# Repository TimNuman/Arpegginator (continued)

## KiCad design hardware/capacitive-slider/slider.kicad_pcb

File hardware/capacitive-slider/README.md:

# Capacitive Touch Slider — AT42QT2120

Hardware design for a no-moving-parts capacitive touch slider PCB that replaces
the on-screen TouchStrip in the Arpegginator. Connects to Teensy 4.1 over I2C.

## Overview

- **IC**: Microchip AT42QT2120 (12-channel capacitive touch controller)
- **Interface**: I2C (addr 0x1C), up to 400 kHz
- **Supply**: 1.8–5.5 V (run at 3.3 V from Teensy)
- **Output**: Per-key touch status + interpolated slider position
- **Slider channels**: 8 keys configured as a slider (keys 0–7)
- **Extra keys**: Keys 8–11 available for discrete buttons (play, stop, shift, etc.)

## Slider Pad Patterns

Three pattern options are provided below. All assume a **100 mm active length**
and **10 mm PCB width**, single-layer copper on the top side with ground fill on
the bottom.

---

### Pattern A: Interleaved Diamonds (Recommended)

The standard pattern from Microchip's application notes. Best balance of
linearity and noise immunity.

```
  Key0  Key1  Key2  Key3  Key4  Key5  Key6  Key7
  ┌─────────────────────────────────────────────────┐
  │  ◇   ◇   ◇   ◇   ◇   ◇   ◇   ◇   ◇   ◇   ◇  │
  │ ◇ ◇ ◇ ◇ ◇ ◇ ◇ ◇ ◇ ◇ ◇ ◇ ◇ ◇ ◇ ◇ ◇ ◇ ◇ ◇ ◇  │
  │  ◇   ◇   ◇   ◇   ◇   ◇   ◇   ◇   ◇   ◇   ◇  │
  └─────────────────────────────────────────────────┘

  Cross-section (one repeat unit):

      ┌───┐       ┌───┐
     /  A  \     /  B  \        A and B are adjacent channels
    /       \   /       \       Diamond tips interleave
   /    ◆    \ /    ◆    \     so A's falling edge overlaps B's
  /           X           \    rising edge — enables interpolation
  \          / \          /
   \        /   \        /
    \      /     \      /
     \    /       \    /
      \  /         \  /
       \/           \/
```

**Dimensions per diamond:**
- Diamond width: 10 mm (along slider axis)
- Diamond height: 8 mm (across slider width)
- Overlap between adjacent keys: 2.5 mm
- Pitch (center-to-center): 12.5 mm
- Gap between copper edges: 0.3 mm
- 8 keys x 12.5 mm = 100 mm active length

**Trace routing:** Each diamond connects via a thin trace (0.2 mm) routed on the
same layer to the AT42QT2120 pin. Keep traces short and add a ground guard ring
around each trace.

---

### Pattern B: Chevron / Zigzag

Higher edge density gives better sensitivity for lighter touches. Slightly more
complex to route.

```
  Key0  Key1  Key2  Key3  Key4  Key5  Key6  Key7
  ┌─────────────────────────────────────────────────┐
  │ /\/\/\/\/\/\/\/\/\/\/\/\/\/\/\/\/\/\/\/\/\/\/\  │
  │ \/\/\/\/\/\/\/\/\/\/\/\/\/\/\/\/\/\/\/\/\/\/\/  │
  │ /\/\/\/\/\/\/\/\/\/\/\/\/\/\/\/\/\/\/\/\/\/\/\  │
  │ \/\/\/\/\/\/\/\/\/\/\/\/\/\/\/\/\/\/\/\/\/\/\/  │
  └─────────────────────────────────────────────────┘

  Cross-section:

  Channel A    Channel B
    /\    /\    /\    /\
   /  \  /  \  /  \  /  \
  /  A \/  B \/  A \/  B \    Interlocking zigzag teeth
  \    /\    /\    /\    /    3-4 teeth per channel
   \  /  \  /  \  /  \  /
    \/    \/    \/    \/
```

**Dimensions:**
- Tooth height: 4 mm
- Tooth pitch: 2.5 mm
- 3 teeth per key, keys spaced at 12.5 mm
- Gap: 0.3 mm

---

### Pattern C: Simple Rectangular Bars

Easiest to lay out. Lower interpolation quality but perfectly adequate for
scrolling. Good starting point if this is your first capacitive PCB.

```
  Key0  Key1  Key2  Key3  Key4  Key5  Key6  Key7
  ┌─────────────────────────────────────────────────┐
  │ ████  ████  ████  ████  ████  ████  ████  ████ │
  │ ████  ████  ████  ████  ████  ████  ████  ████ │
  │ ████  ████  ████  ████  ████  ████  ████  ████ │
  └─────────────────────────────────────────────────┘

  Cross-section:

  ┌──────┐ ┌──────┐ ┌──────┐
  │      │ │      │ │      │   Simple rectangular pads
  │  A   │ │  B   │ │  C   │   with gaps between them.
  │      │ │      │ │      │   Interpolation uses signal
  └──────┘ └──────┘ └──────┘   strength ratio of neighbors.
     gap      gap      gap
```

**Dimensions:**
- Pad width: 11 mm (along slider axis)
- Pad height: 8 mm
- Gap: 1.5 mm
- Pitch: 12.5 mm

---

## Schematic

```
                          AT42QT2120
                     ┌──────────────────┐
  Teensy SDA ───────┤ SDA          KEY0 ├─── Slider pad 0
  Teensy SCL ───────┤ SCL          KEY1 ├─── Slider pad 1
                    │              KEY2 ├─── Slider pad 2
  3.3V ──┬─────────┤ VDD          KEY3 ├─── Slider pad 3
         │  100nF  │              KEY4 ├─── Slider pad 4
         ├──||─────┤ VSS (GND)    KEY5 ├─── Slider pad 5
         │         │              KEY6 ├─── Slider pad 6
  GND ───┴─────────┤ VSS          KEY7 ├─── Slider pad 7
                    │                   │
                    │ CHANGE# ──────────┼─── Teensy GPIO (interrupt)
                    │                   │
                    │ KEY8  ─────────── ┼─── (optional: Play btn)
                    │ KEY9  ─────────── ┼─── (optional: Stop btn)
                    │ KEY10 ─────────── ┼─── (optional: Shift btn)
                    │ KEY11 ─────────── ┼─── (optional: Mode btn)
                    │                   │
                    │ MODE  ─────────── ┼─── GND (I2C mode)
                    └──────────────────┘

  Pull-ups: 4.7 kOhm on SDA and SCL to 3.3V
  Decoupling: 100 nF + 10 uF on VDD/VSS
```

## Bill of Materials

| Ref  | Part              | Package    | Qty | Notes                         |
|------|-------------------|------------|-----|-------------------------------|
| U1   | AT42QT2120-MMH    | QFN-24     | 1   | Capacitive touch controller   |
| C1   | 100 nF ceramic    | 0402/0603  | 1   | VDD decoupling                |
| C2   | 10 uF ceramic     | 0805       | 1   | VDD bulk decoupling           |
| R1   | 4.7 kOhm         | 0402/0603  | 1   | I2C SDA pull-up               |
| R2   | 4.7 kOhm         | 0402/0603  | 1   | I2C SCL pull-up               |
| J1   | 4-pin header      | 2.54mm     | 1   | VCC, GND, SDA, SCL (+ CHANGE#)|
| --   | PCB copper pads   | --         | 8   | Slider electrode pattern      |

**Total component cost: ~$2-3**

## PCB Layout Guidelines

1. **Ground plane**: Solid ground on bottom layer. Do NOT place ground copper
   directly under the slider pads — leave a keepout zone. Ground surrounds
   the pads but doesn't overlap.

2. **Overlay**: Apply solder mask over the slider pads for a smooth touch
   surface. The 35 um solder mask acts as a thin dielectric — sensitivity
   remains excellent through it.

3. **Trace routing**: Keep sense traces short (<20 mm). Route away from noisy
   signals (PWM, clocks). Add ground guard traces between sense traces.

4. **Board thickness**: Standard 1.6 mm FR4 is fine. Thinner (0.8 mm) gives
   slightly better sensitivity but isn't necessary.

5. **Finger contact area**: The slider should be at least 8 mm wide to ensure
   reliable finger detection.

6. **IC placement**: Place AT42QT2120 at one end of the slider strip, close to
   the connector. This minimizes trace length to the connector.

## AT42QT2120 Register Configuration

To configure keys 0-7 as a slider, write these registers at startup:

| Register | Value  | Description                                    |
|----------|--------|------------------------------------------------|
| 0x00     | (read) | Chip ID — should return 0x3E                   |
| 0x0E     | 0x08   | Slider control: enable slider, 8 keys          |
| 0x10-17  | 0x04   | Per-key threshold (lower = more sensitive)      |
| 0x1E-25  | 0x00   | Per-key detect integrator (0 = default 4)       |
| 0x06     | (read) | Slider position: 0-255                          |

The slider position register (0x06) returns 0-255, which is used directly
by the Arpegginator strip engine (native 0-255 range):

```rust
let pos = i2c_read_reg(0x1C, 0x06) as i32;  // 0-255, used as-is
```

## Teensy 4.1 Wiring

| Teensy Pin | Signal   | Notes                    |
|------------|----------|--------------------------|
| 18 (SDA0)  | SDA     | I2C bus 0                |
| 19 (SCL0)  | SCL     | I2C bus 0                |
| 2 (GPIO)   | CHANGE# | Active-low interrupt     |
| 3.3V       | VDD     | Power                    |
| GND        | VSS     | Ground                   |

## Two Sliders

The Arpegginator uses two strips (vertical + horizontal). Options:

1. **Two AT42QT2120s**: Each on its own I2C address — but the AT42QT2120 has
   a fixed address (0x1C). Use an I2C multiplexer (TCA9548A) or...

2. **One AT42QT2120, split keys**: Use keys 0-3 as slider A (vertical,
   4 keys) and keys 4-7 as slider B (horizontal, 4 keys). Lower resolution
   per slider but simpler. The chip supports configuring two separate sliders.

3. **Two PCBs + TCA9548A mux**: Cleanest solution. Each slider is an
   independent 8-key strip. The mux adds one more IC but gives full resolution
   on both axes.

**Recommendation**: Option 3 if you want full resolution on both. Option 2 if
you want a single board.

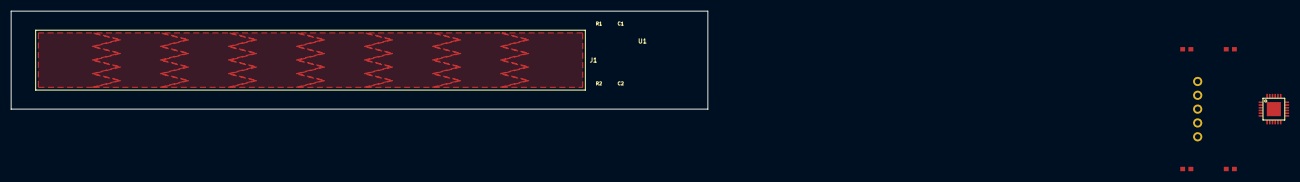
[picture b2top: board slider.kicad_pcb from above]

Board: 2 copper layers, 128.0 x 18.0 mm, 6 parts (0 on the bottom side), 5 nets, no tracks yet.

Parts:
C1: 100nF; C_0603
C2: 10uF; C_0603
J1: CONN; PinHeader_1x05_P2.54mm
R1, R2: 4.7k; C_0603
U1: AT42QT2120; AT42QT2120-MMH

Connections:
CHANGE: J1.5, U1.6
GND: C1.2, C2.2, J1.2, U1.1, U1.4, U1.18, U1.25
SCL: J1.4, R2.2, U1.5
SDA: J1.3, R1.2, U1.3
VCC: C1.1, C2.1, J1.1, R1.1, R2.1, U1.16

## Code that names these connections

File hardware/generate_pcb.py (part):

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# 26     : GND
# 27     : LED_DIN  (data input to first LED)
# 28-154 : LED_CHAIN_1..LED_CHAIN_127 (DOUT→DIN between consecutive LEDs)
# 155-282: SW_0_0..SW_7_15 (switch pin 2 → diode anode)
# 283    : I2C_SDA       (MPR121 touch controllers)
# 284    : I2C_SCL       (MPR121 touch controllers)

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def col_pin_pos(c):
    """Target position for COL c on U1 (rotated 45°).

    Port A: GPA0(pin21) + GPA1-7(pins22-28) → COL0-7
    Port B: GPB0-6(pins1-7) + GPB7(pin8) → COL8-15
    """
    if c == 0:    return qfn_pin_pos(U1_X, U1_Y, 21, QFN_ROTATION)
    elif c <= 7:  return qfn_pin_pos(U1_X, U1_Y, 21 + c, QFN_ROTATION)
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def row_pin_pos(r):
    """Target position for ROW r on U2 (rotated 45°).

    Port A: GPA0(pin21) + GPA1-7(pins22-28) → ROW0-7
    """
    if r == 0:  return qfn_pin_pos(U2_X, U2_Y, 21, QFN_ROTATION)
    else:       return qfn_pin_pos(U2_X, U2_Y, 21 + r, QFN_ROTATION)
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

def route_conn_led_din():
    """LED_DIN from first LED to Teensy pin 1."""
    return ""


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
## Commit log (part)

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2026-03-06 Fix note rendering
2026-03-06 scrubbing highlights
2026-03-06 deploy: 2cc6cc97c2ce5275c9d79fbbd0bf35b418953072
2026-03-07 Add key bindings and OLED legends for clock settings
    In modify mode with a note selected:
    - Shift+Up/Down: toggle clock mode (Hit ↔ Clock)
    - Shift+Left/Right: adjust clock speed (musical divisions)
    - Ctrl+Up/Down: cycle clock trigger (Free → Note → Loop)
    OLED legends update contextually:
    - Hold Shift: shows Clock mode and Speed controls
2026-03-07 Add timed clock progression for sub-mode arrays
    Sub-mode arrays can now advance based on ticks instead of per-hit.
    Three new fields on SubModeArray:
    - clock_mode: Hit (default, per-note) or Clock (tick-based)
    - clock_speed: ticks per array step (1-255, default 12)
    - clock_trigger: Free (from transport start), Note (from event
    position), or Loop (resets at loop start)
2026-03-07 TS cleanup
2026-03-08 Add Conway's Game of Life playback mode
    Adds a per-channel Game of Life mode inspired by Conway. When no note is
    selected in Pattern mode, press Shift+Up or Shift+Down to toggle between
    normal and Game of Life playback. The current visible notes seed the GoL
    grid. During playback, alive cells trigger notes as the playhead sweeps
    columns, and the grid evolves one generation on each loop boundary.
    https://claude.ai/code/session_01KodyJyVgz87rUB9VkYuGV7
2026-03-08 Add unit tests for Game of Life toggle and evolution
    Tests verify: direct toggle, Shift+Arrow toggle via arrow press,
    and blinker oscillator evolution correctness.
    https://claude.ai/code/session_01KodyJyVgz87rUB9VkYuGV7
2026-03-08 Allow toggling GoL cells by clicking grid buttons
    When Game of Life mode is active, clicking a grid button toggles that
    cell alive/dead directly instead of creating/selecting pattern notes.
    https://claude.ai/code/session_01KodyJyVgz87rUB9VkYuGV7
2026-03-08 Extend GoL grid to full 128-row height with vertical scrolling
    The GoL grid now covers the entire note range (128 rows) instead of
    just the visible 8 rows. Scrolling vertically shows different slices
    of the full grid, and drawing/playback maps correctly through the
    scroll offset.
    - GOL_ROWS constant (128) for grid height
    - gol_evolve/neighbors use full grid with toroidal wrap
2026-03-08 Clear GoL grid when clear pattern (trashcan) is pressed
    https://claude.ai/code/session_01KodyJyVgz87rUB9VkYuGV7
2026-03-09 Clean up GoL mode OLED display
    - Without shift: just show "CH x" without the "- LIFE/NORMAL" suffix
    - With shift: show "MODE NORMAL LIFE" with the active one highlighted red
    https://claude.ai/code/session_01KodyJyVgz87rUB9VkYuGV7
2026-03-09 Keep dash cyan in channel row, only color the mode name
    https://claude.ai/code/session_01KodyJyVgz87rUB9VkYuGV7
2026-03-09 Replace loop mode
2026-03-09 Sort scales
2026-03-09 Zooming out sticks to loop
2026-03-10 Auto increase repeatAmount when setting repeatSpace if needed
2026-03-10 UX fixes
2026-03-10 More randomisation options
2026-03-10 Randomization fixes
2026-03-10 Fix highlighting for offscreen notes
2026-03-11 Update loop edit functionality
2026-03-11 More fixes
2026-03-12 Add a few arp styles
2026-03-12 Drum randomness
2026-03-13 Option to compare used notes across channels and improve colors
2026-03-13 Improve mod mode switching
2026-03-13 Improve mod mode defaults and keys
2026-03-13 Add stay to mod mode
2026-03-15 deploy: 9c742b8a8afed3292781a0940c438ab61fa36d2f
2026-03-15 Rename to Arpegginator everywhere
2026-03-15 deploy: d91130b725f00b15abe552762e2dc5ebce7ed1c8
2026-03-16 deploy: 41e55b6d2bd5c8df907fad100454b0f1b13a520e
2026-03-18 New OLED and control refactor
2026-03-18 Mod modes screen update
2026-03-19 deploy: dd7aa83f2385a29b115ad65c4610968995ddfbe0
2026-03-19 deploy: aa45711c9e64d9a8d63447d6f185e45a14596401
2026-03-19 CoF line thickness
2026-03-19 No more alloc
2026-03-20 deploy: 395ed81f18655fc1a828fbfbce97e8ebb06c6968
2026-03-20 deploy: 2d1de3d1c2aa461a60a68a51235a1dc2321a52f1
2026-03-22 deploy: f0e5e428dd901ba133d1915e5d429b0d06472b6b
2026-03-22 Fix oled inv highlighting
2026-03-22 Fix vel/hit colors
2026-03-23 Move ChannelColors to rust
2026-03-23 Clean up fonts
2026-03-23 More cleanup
2026-03-23 deploy: 8d40c29fa4e44b3941fed5d1d3b8647e016fa784
2026-03-23 Teensy target
2026-03-25 Remove duplicate isTeensy branch in play() — both paths were identical
    Both WASM and Teensy need the local tick loop for grid rendering.
    Keep the comment explaining why.
    https://claude.ai/code/session_01FUrQ1EuLYi3ZbaoU9Wj9aN
2026-03-25 Use functional patterns and simplify conditionals across codebase
    - TeensyEngine: Array.from for channel types, .forEach for rowOffsets
    - WasmEngine: Array.from for fieldOffsets, extract toGrid() helper for
    readGridBuffers nested loop
    - midiProtocol: Math.abs instead of manual ternary, Array.from for
    rowOffsets decoding
    - Grid.helpers: single return expression for encodeModifiers
2026-03-25 Replace engine! non-null assertions with early returns via readyEngine()
    Renamed engineReady() to readyEngine() which returns Engine | null,
    enabling proper type narrowing. Each function binds `const e = readyEngine()`
    and early-returns if null, eliminating all `engine!.` assertions.
    setBpm/setSwing simplified to one-liners with optional chaining.
    https://claude.ai/code/session_01FUrQ1EuLYi3ZbaoU9Wj9aN
2026-03-25 deploy: e5300d7db3dd81ab6da4f10272019e95a2559566
2026-03-25 Remove unused fieldOffsets and _getFieldOffset from WasmEngine
    These were written but never read — the Array.from refactor surfaced
    the TS6133 warning that the old mutation-based loop hid.
    https://claude.ai/code/session_01FUrQ1EuLYi3ZbaoU9Wj9aN
2026-03-25 deploy: f4da66b7f1070f0d8cca01f5ae6f72cb2a760988
2026-03-25 Clean up TypeScript: remove dead code, simplify patterns (#10)
2026-03-25 deploy: 8261deae194437d50a847f7340979d6e1565cbc7
2026-03-25 Add AT42QT2120 capacitive touch slider hardware design
    PCB design guide with three pad pattern options (diamond, chevron, rectangular),
    full schematic, BOM, layout guidelines, and register configuration for the
    AT42QT2120. Includes a Rust driver that emits Start/Move/End events compatible
    with the existing strip engine protocol.
    https://claude.ai/code/session_01ExJ7gFQfT848CsR2EsnjBp
2026-03-25 deploy: 38177e9dc6e4793cde476551104451eebd692f35
2026-03-25 deploy: 14be885eeb1d1321db3394d9fb52b7076c97fd18
2026-03-28 Add 16x8 button grid PCB with Choc switches, RGBW LEDs, and anti-ghosting diodes
    - generate_pcb.py: parametric generator for the full 128-key grid
    - button_grid.kicad_pcb: 320x172mm board with Kailh Choc v1 switches at
    19.05mm spacing, SK6812MINI-E RGBW LEDs in a snaking chain, 1N4148W
    SOD-323 diodes per key, and pin header connectors (16 col + 8 row + power)
    - Matrix scanning uses 24 GPIO pins, LED chain uses 1 data pin
    https://claude.ai/code/session_01ExJ7gFQfT848CsR2EsnjBp
2026-03-28 deploy: 83f9db6038f5770457f3f4fde6bbb1cace503987
2026-03-30 Add full trace routing to button grid PCB
    Routing (1117 traces, 639 vias):
    - F.Cu column buses with dogleg around center posts
    - F.Cu switch-to-diode traces
    - B.Cu row buses with vias at diode cathodes
    - B.Cu LED data chain (snaking, intra-row channel + inter-row margin routing)
    - B.Cu LED VCC bus (0.5mm power traces at cy-4.5mm per row)
2026-03-30 Fix KiCad 8 compatibility: update version and keepout zone syntax
    - Bump format version from 20221018 (KiCad 7) to 20240108 (KiCad 8)
    - Replace old (zone ... (attr (is_rule_area))) with (rule_area ...) syntax
    for the slider keepout zone, matching KiCad 8's expected format
    https://claude.ai/code/session_01ExJ7gFQfT848CsR2EsnjBp
2026-03-30 Remove keepout zone from slider PCB to fix KiCad compatibility
    The keepout zone syntax varies across KiCad versions. Removed it from
    the generated file — add manually in KiCad's PCB editor if needed.
    https://claude.ai/code/session_01ExJ7gFQfT848CsR2EsnjBp
2026-03-30 Tracing
2026-03-31 Better components
2026-03-31 deploy: 6f342248bc79888a9fc9ab3da447720ec877fee5
2026-03-31 Improve pcb
2026-04-01 Trace bottom buttons
2026-04-02 PCB tweaks + bom generator
2026-04-02 Update PCB
2026-04-07 Switch matrix expanders from MCP23017 (I2C) to MCP23S17 (SPI)
    Replace I2C-based MCP23017 I/O expanders with SPI-based MCP23S17 for
    lower-latency matrix scanning (~0.2ms vs ~6.4ms). The MCP23S17 shares
    the SPI0 bus with the ILI9341 display, using dedicated CS lines on
    Teensy pins 20/21. I2C bus retained for MPR121 touch controllers.
    https://claude.ai/code/session_018rK8iTfeExxTRFFAroWHDj
2026-05-16 Regenerate BOM with updated timestamp
    https://claude.ai/code/session_018rK8iTfeExxTRFFAroWHDj
2026-05-16 deploy: f19fbc49119191fd78d0ea5863fa167039c8da99
2026-05-16 Generate latest version kicad file
2026-06-13 Harden Rust engine against host-reachable memory-safety bugs
    The engine is driven by an untrusted host: the JS frontend writes engine
    state directly through raw buffer pointers, and the Teensy firmware accepts
    SysEx from any connected DAW. With panic = "abort" in release, any
    out-of-bounds index traps the whole WASM module or halts the firmware, so
    these are treated as reachable inputs.
    Critical (crashes / corruption):
2026-06-13 Refactor Rust engine to safe code over a single unsafe boundary
    The engine relied on crate-wide #![allow(static_mut_refs)] and scattered
    unsafe blocks, mostly around the JS/WASM bridge globals. Introduce
    Global<T> (engine/src/cell.rs) — one audited, zero-cost interior-mutability
    cell justified by the single-threaded execution model — and route all
    global mutable state through it. The rest of the code becomes ordinary
    safe Rust and the allow attributes are removed.
2026-06-13 Keep explanatory comments only in the unsafe layer (cell.rs)
    Strip the inline commentary added to safe-Rust sites in the previous
    commit; the rationale lives in cell.rs where the unsafe is concentrated.
2026-06-13 Fix critical host-input crashes and pool corruption (review items 1-6)
    The engine takes host input directly — JS writes raw buffer pointers and
    the Teensy takes SysEx — and the workspace builds with panic = "abort",
    so an out-of-bounds index traps the whole module. Harden the reachable
    paths:
    1. Channel mode indexed 8 grid rows into 6-channel arrays. Guard
    handle_channel_press (ch_idx >= NUM_CHANNELS) and dim the extra rows
2026-06-13 Fix WASM cdylib link: import undefined js_* host symbols
    CI's newer wasm-ld no longer auto-imports undefined extern "C" function
    symbols, so linking the cdylib failed with 'undefined symbol:
    js_set_current_tick' (and the other six JS bridge imports declared in
    platform.rs). Pass --import-undefined so wasm-ld generates WebAssembly
    imports for them; they resolve under the default 'env' module, matching
    the importObject.env the JS side provides in WasmEngine.ts.
2026-06-13 deploy: a5cf89a51863e1063c2cf82ef3415c0b8c480bff
2026-06-13 Add npm scripts for Teensy build and flash
    - build:teensy compile firmware only (thumbv7em release)
    - flash:teensy build + flash, manual bootloader button (build_flash.sh)
    - flash:teensy:reboot build + flash button-less via MIDI reboot (flash.sh)
2026-06-13 Cleanup wasm
2026-06-13 deploy: c430b63d46f38e24447fe862c9ca3a1dc997586b
2026-06-13 All timing to rust
2026-06-13 More to teensy
